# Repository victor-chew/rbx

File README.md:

# RBX

### What is RBX?

[RBX](https://rbx.randseq.org/) (*Robotics Brick Extension*) is a robotics kit designed for young tinkerers. It consists of a set of Lego-compatible "bricks" made with common  [Arduino](https://www.arduino.cc/)  components, such as LED, pushbutton, servo, motor etc. The brick housing are printed using a 3D printer. The RBX bricks are hooked up to a microcontroller via standardized "ports". Programming is done via a variant of [Javascript](https://duktape.org) on a browser-based IDE.

 [")](https://rbx.randseq.org/images/rbx/bricks/rbx-battery-aa.jpg) [")](https://rbx.randseq.org/images/rbx/bricks/rbx-battery-18650.jpg) [")](https://rbx.randseq.org/images/rbx/bricks/rbx-motor-power.jpg)          

### Target audience

The target audience is 8-12 year old children who need something between the simplicity of block-based programming environment such as Lego Mindstorm, and a full-blown IDE such as  [Arduino](https://www.arduino.cc/)  or  [PlatformIO](https://platformio.org/). Not only is Javascript the de-facto scripting language, it also eliminates the long compile-build-run cycle, which is more suited for experimentation with impatient young minds.

### Making hardware accessible

One of the first obstacles for a young student trying to break into microcontroller programming is hooking up the desired circuitry on a breadboard. Anything beyond the the introductory "Hello World" LED example requires a ton of wiring, which is quite a lot to ask for a young child. When servos or motors are involved, a separate power rail is required, which makes things even more complicated.

RBX uses various JST connectors to connect to the microcontroller. These are called "ports", which maps to the microcontroller pins. The ports come in 2, 3 and 4-pin variety, and each port has a unique identifier, Other connectors are used for providing power to motors or servos. In this way, hooking up stuff becomes a plug-and-play affair. Since the connectors need to be matching and oriented correctly, this makes it less likely for modules to be hooked up the wrong way.

### Microntroller

For the microcontroller, the ESP32 is chosen. It is incredibly powerful, and comes with built-in WIFI and bluetooth. The development board is also very affordable, available for only a few dollars online. It has a 2-core processor, and has enough RAM and flash storage to run a Javascript interpreter. It also has many pins available, which lets the microcontroller connect to many components simultaneously.

### Programming made easy

For the JavaScript interpreter,  [Duktape](https://duktape.org/)  was ported to the ESP32.  [Duktape](https://duktape.org/)  has very low resource and memory requirement, which makes it particularly suited for a microcontroller.

A browser-based IDE is served directly from the microcontroller, using  [Ace](https://ace.c9.io/)  as the code editor. Once the microcontroller is powered on, the user is able to connect via a web browser and start running JavaScript code immediately. Code can be saved to the flash storage on the ESP32 and retrieved later.

### Conclusion

In summary, RBX is relatively cheap to make, yet it is far more versatile than most of the pre-built electronic/robotic kits on the market. A young maker can get up to speed with the kit very quickly. As more experience is accumulated, he/she can delve into each of the "bricks" to see what makes them tick, or even make them from scratch.

On the software side, although we start with JavaScript, it is quite easy to switch to  [Arduino](https://www.arduino.cc/)  for more complex projects. At the root of RBX is an  [Arduino](https://www.arduino.cc/)  library, which is pretty straightforward to engage with directly for a more experienced  [Arduino](https://www.arduino.cc/)  programmer.

### Resources

 - [RBX website](https://rbx.randseq.org/)
 - [Sample projects](https://rbx.randseq.org/index.php/blinking-led)

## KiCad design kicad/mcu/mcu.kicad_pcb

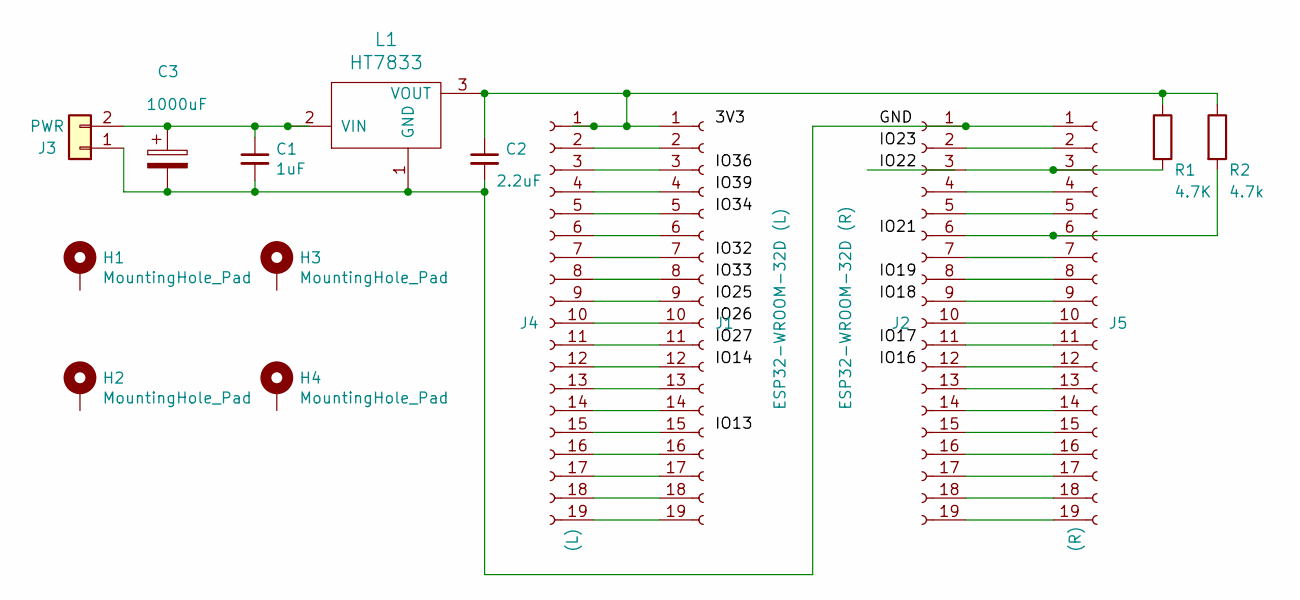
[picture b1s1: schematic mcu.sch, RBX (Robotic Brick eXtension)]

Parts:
C1: 1uF; C_Disc_D3.0mm_W1.6mm_P2.50mm
C2: 2.2uF; C_Disc_D3.0mm_W1.6mm_P2.50mm
C3: 1000uF; CP_Radial_D4.0mm_P2.00mm
H1, H2, H3, H4: MountingHole_Pad; MountingHole_2.5mm_Pad
J1: ESP32-WROOM-32D (L); PinSocket_1x19_P2.54mm_Vertical
J2: ESP32-WROOM-32D (R); PinSocket_1x19_P2.54mm_Vertical
J3: PWR; PinSocket_1x02_P2.54mm_Vertical
J4: (L); PinSocket_1x19_P2.54mm_Vertical
J5: (R); PinSocket_1x19_P2.54mm_Vertical
L1: HT7833; TO-92
R1: 4.7K; R_Axial_DIN0204_L3.6mm_D1.6mm_P5.08mm_Horizontal
R2: 4.7k; R_Axial_DIN0204_L3.6mm_D1.6mm_P5.08mm_Horizontal

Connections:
/GND: C1.2, C2.2, C3.2, J2.1, J3.1, J5.1, L1.1 (GND)
unnamed: C1.1, C3.1, J3.2, L1.2 (VIN)
unnamed: C2.1, J1.1, J4.1, L1.3 (VOUT), R1.1, R2.1
unnamed: J1.2, J4.2
unnamed: J1.3, J4.3
unnamed: J1.4, J4.4
unnamed: J1.5, J4.5
unnamed: J1.6, J4.6
unnamed: J1.7, J4.7
unnamed: J1.8, J4.8
unnamed: J1.9, J4.9
unnamed: J1.10, J4.10
unnamed: J1.11, J4.11
unnamed: J1.12, J4.12
unnamed: J1.13, J4.13
unnamed: J1.14, J4.14
unnamed: J1.15, J4.15
unnamed: J1.16, J4.16
unnamed: J1.17, J4.17
unnamed: J1.18, J4.18
unnamed: J1.19, J4.19
unnamed: J2.2, J5.2
unnamed: J2.3, J5.3, R1.2
unnamed: J2.4, J5.4
unnamed: J2.5, J5.5
unnamed: J2.6, J5.6, R2.2
unnamed: J2.7, J5.7
unnamed: J2.8, J5.8
unnamed: J2.9, J5.9
unnamed: J2.10, J5.10
unnamed: J2.11, J5.11
unnamed: J2.12, J5.12
unnamed: J2.13, J5.13
unnamed: J2.14, J5.14
unnamed: J2.15, J5.15
unnamed: J2.16, J5.16
unnamed: J2.17, J5.17
unnamed: J2.18, J5.18
unnamed: J2.19, J5.19

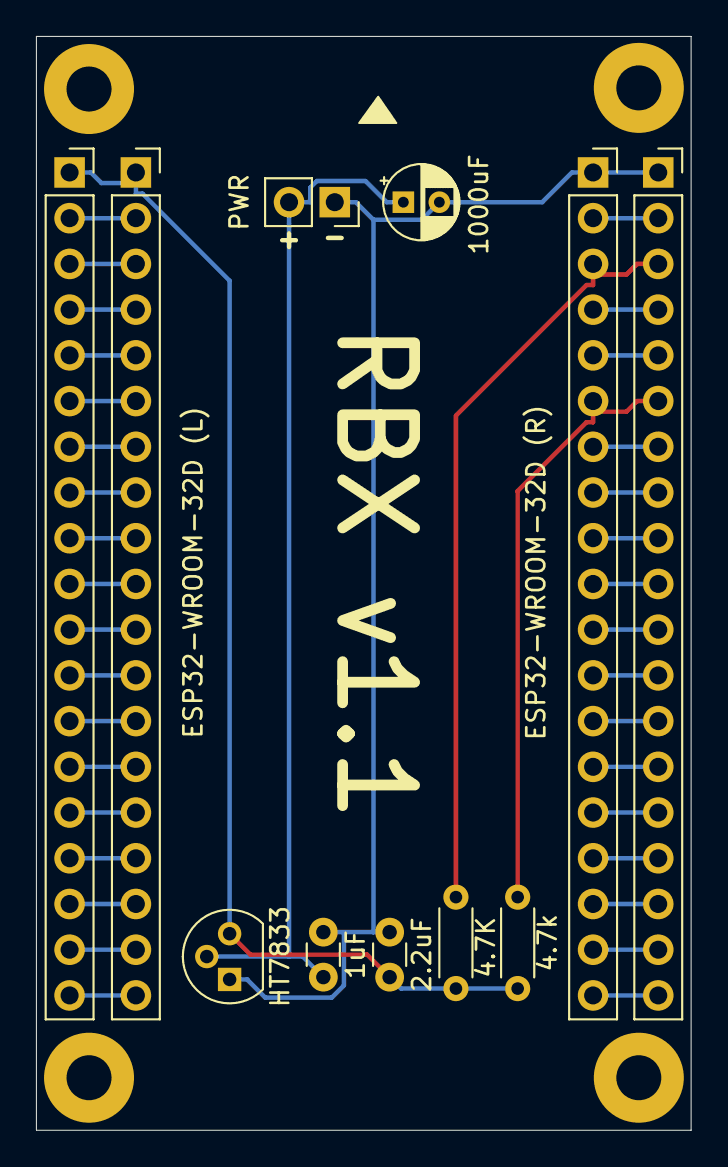
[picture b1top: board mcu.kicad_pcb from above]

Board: 2 copper layers, 36.4 x 60.8 mm, 15 parts (0 on the bottom side), 39 nets.

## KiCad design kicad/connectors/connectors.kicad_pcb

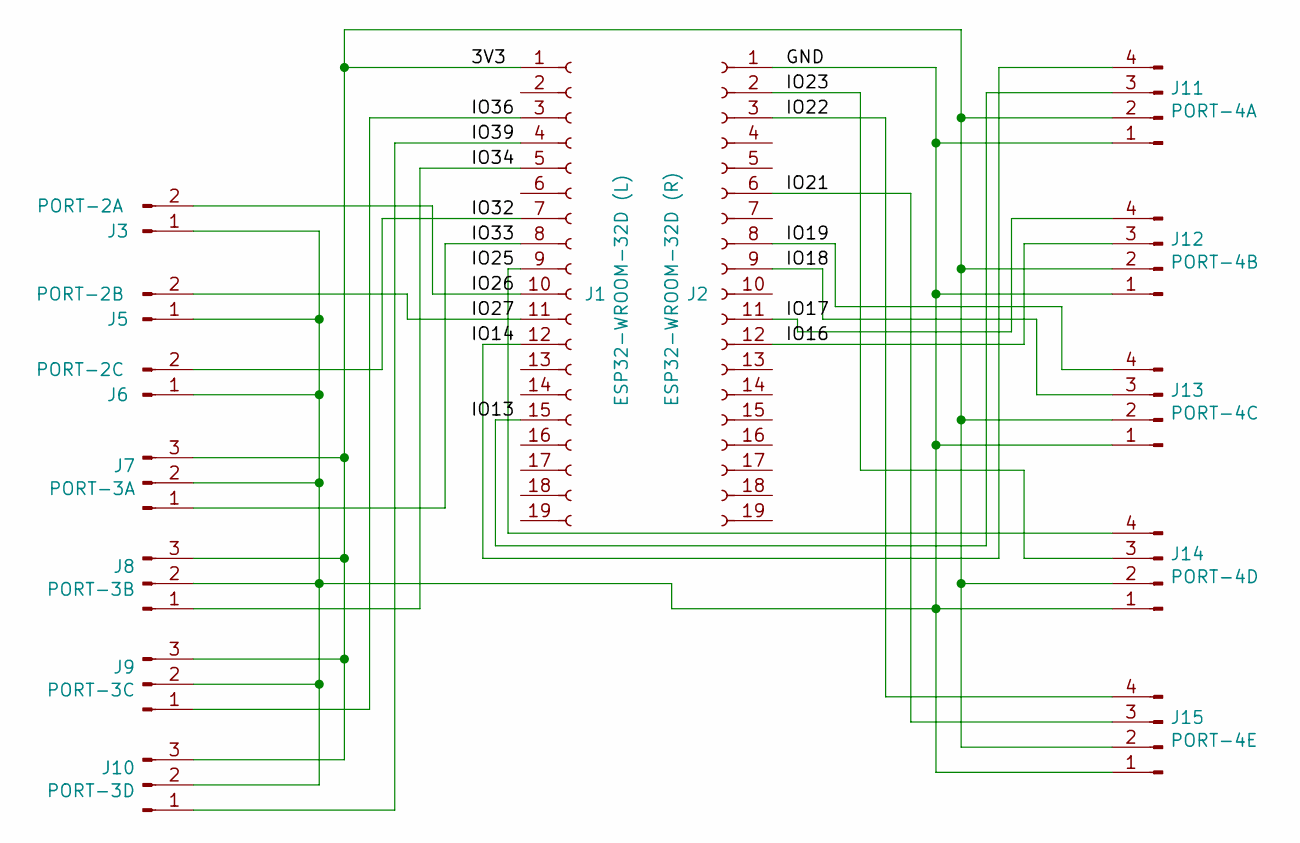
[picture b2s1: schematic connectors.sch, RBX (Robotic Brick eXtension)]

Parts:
J1: ESP32-WROOM-32D (L); PinSocket_1x19_P2.54mm_Vertical
J2: ESP32-WROOM-32D (R); PinSocket_1x19_P2.54mm_Vertical
J3: PORT-2A; JST_XH_B2B-XH-A_1x02_P2.50mm_Vertical
J5: PORT-2B; JST_XH_B2B-XH-A_1x02_P2.50mm_Vertical
J6: PORT-2C; JST_XH_B2B-XH-A_1x02_P2.50mm_Vertical
J7: PORT-3A; JST_XH_B3B-XH-A_1x03_P2.50mm_Vertical
J8: PORT-3B; JST_XH_B3B-XH-A_1x03_P2.50mm_Vertical
J9: PORT-3C; JST_XH_B3B-XH-A_1x03_P2.50mm_Vertical
J10: PORT-3D; JST_XH_B3B-XH-A_1x03_P2.50mm_Vertical
J11: PORT-4A; JST_XH_B4B-XH-A_1x04_P2.50mm_Vertical
J12: PORT-4B; JST_XH_B4B-XH-A_1x04_P2.50mm_Vertical
J13: PORT-4C; JST_XH_B4B-XH-A_1x04_P2.50mm_Vertical
J14: PORT-4D; JST_XH_B4B-XH-A_1x04_P2.50mm_Vertical
J15: PORT-4E; JST_XH_B4B-XH-A_1x04_P2.50mm_Vertical

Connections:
/3V3: J1.1, J7.3, J8.3, J9.3, J10.3, J11.2, J12.2, J13.2, J14.2, J15.2
/GND: J2.1, J3.1, J5.1, J6.1, J7.2, J8.2, J9.2, J10.2, J11.1, J12.1, J13.1, J14.1, J15.1
/IO16: J2.12, J12.3
/IO17: J2.11, J12.4
/IO18: J2.9, J13.3
/IO19: J2.8, J13.4
/IO21: J2.6, J15.3
/IO22: J2.3, J15.4
/IO23: J2.2, J14.3
/IO26: J1.10, J3.2
/IO27: J1.11, J5.2
/IO32: J1.7, J6.2
/IO33: J1.8, J7.1
/IO34: J1.5, J8.1
/IO36: J1.3, J9.1
/IO39: J1.4, J10.1
unnamed: J1.9, J14.4
unnamed: J1.12, J11.4
unnamed: J1.15, J11.3

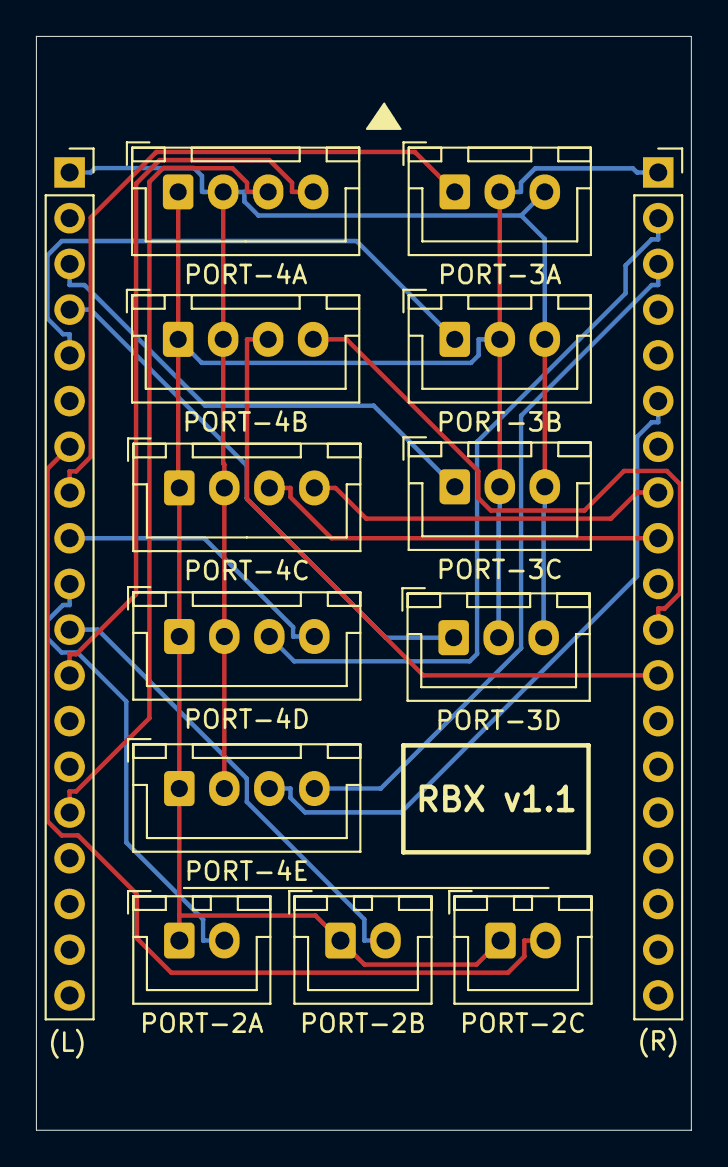
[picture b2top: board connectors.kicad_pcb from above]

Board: 2 copper layers, 36.4 x 60.8 mm, 14 parts (0 on the bottom side), 19 nets.
